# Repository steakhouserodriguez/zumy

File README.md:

# zumy
Zumy is a small robot running linux using Pololu's Zumo robot chassis.

For Instructions, see the [Wiki](https://github.com/andrewjchen/zumy/wiki)

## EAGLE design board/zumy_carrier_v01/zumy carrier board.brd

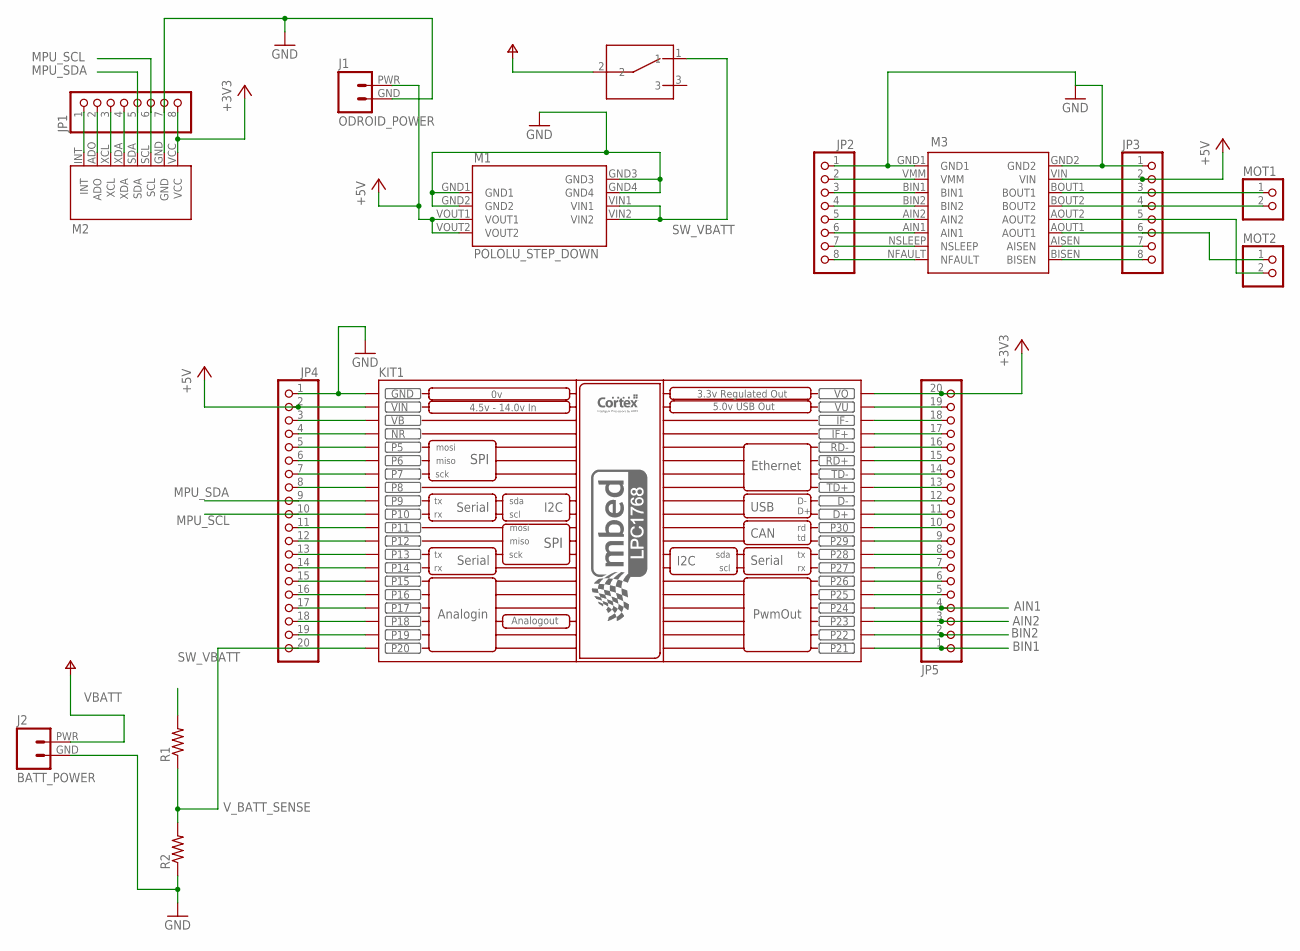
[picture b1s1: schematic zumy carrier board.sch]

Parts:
J1: ODROID_POWER; ODOIRD_PWR
J2: BATT_POWER
JP1, JP2, JP3: PINHD-1X8; 1X08
JP4, JP5: PINHD-1X20; 1X20
KIT1: MBED_NXP_LPC1768; MBED-KIT
M1: POLOLU_STEP_DOWN
M2: ITG/MPU_MODULE
M3: POLOLU_DRV8833_MODULE
MOT1, MOT2: PINHD-1X2; 1X02
R1, R2: R-US_0204/5; 0204/5
SW1: 500SSP1S1M6QEA; 500SSP1S1M6QEA_SWITCH

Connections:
+3V3: JP1.8, JP5.20, KIT1.VOUT (VO), M2.VCC
+5V: J1.PWR, JP3.2, JP4.2, KIT1.VIN, M1.VOUT1, M1.VOUT2, M3.VIN
AIN1: JP2.6, JP5.4, KIT1.P$24 (P24), M3.AIN1
AIN2: JP2.5, JP5.3, KIT1.P$23 (P23), M3.AIN2
BIN1: JP2.3, JP5.1, KIT1.P$21 (P21), M3.BIN1
BIN2: JP2.4, JP5.2, KIT1.P$22 (P22), M3.BIN2
GND: J1.GND, J2.GND, JP1.7, JP2.1, JP3.1, JP4.1, KIT1.GND, M1.GND1, M1.GND2, M1.GND3, M1.GND4, M2.GND, M3.GND1, M3.GND2, R2.1
MPU_SCL: JP1.6, JP4.10, KIT1.P$10 (P10), M2.SCL
MPU_SDA: JP1.5, JP4.9, KIT1.P$9 (P9), M2.SDA
unnamed: JP1.1, M2.INT
unnamed: JP1.2, M2.ADO
unnamed: JP1.3, M2.XCL
unnamed: JP1.4, M2.XDA
unnamed: JP4.15, KIT1.P$15 (P15)
unnamed: JP4.3, KIT1.VB
unnamed: JP4.4, KIT1.NR
unnamed: JP4.5, KIT1.P$5 (P5)
unnamed: JP4.6, KIT1.P$6 (P6)
unnamed: JP4.7, KIT1.P$7 (P7)
unnamed: JP4.8, KIT1.P$8 (P8)
unnamed: JP4.11, KIT1.P$11 (P11)
unnamed: JP4.12, KIT1.P$12 (P12)
unnamed: JP4.13, KIT1.P$13 (P13)
unnamed: JP4.14, KIT1.P$14 (P14)
unnamed: JP4.16, KIT1.P$16 (P16)
unnamed: JP4.17, KIT1.P$17 (P17)
unnamed: JP4.18, KIT1.P$18 (P18)
unnamed: JP4.19, KIT1.P$19 (P19)
unnamed: JP5.5, KIT1.P$25 (P25)
unnamed: JP5.6, KIT1.P$26 (P26)
unnamed: JP5.7, KIT1.P$27 (P27)
unnamed: JP5.8, KIT1.P$28 (P28)
unnamed: JP5.9, KIT1.P$29 (P29)
unnamed: JP5.10, KIT1.P$30 (P30)
unnamed: JP5.11, KIT1.D+
unnamed: JP5.12, KIT1.D-
unnamed: JP5.13, KIT1.TD+
unnamed: JP5.14, KIT1.TD-
unnamed: JP5.15, KIT1.RD+
unnamed: JP5.16, KIT1.RD-
unnamed: JP5.17, KIT1.IF+
unnamed: JP5.18, KIT1.IF-
unnamed: JP5.19, KIT1.VU
unnamed: JP2.2, M3.VMM
unnamed: JP2.7, M3.NSLEEP
unnamed: JP2.8, M3.NFAULT
unnamed: JP3.3, M3.BOUT1, MOT1.1
unnamed: JP3.4, M3.BOUT2, MOT1.2
unnamed: JP3.5, M3.AOUT2, MOT2.2
unnamed: JP3.6, M3.AOUT1, MOT2.1
unnamed: JP3.7, M3.AISEN
unnamed: JP3.8, M3.BISEN
SW_VBATT: M1.VIN1, M1.VIN2, R1.2, SW1.1
VBATT: J2.PWR, SW1.2
V_BATT_SENSE: JP4.20, KIT1.P$20 (P20), R1.1, R2.2

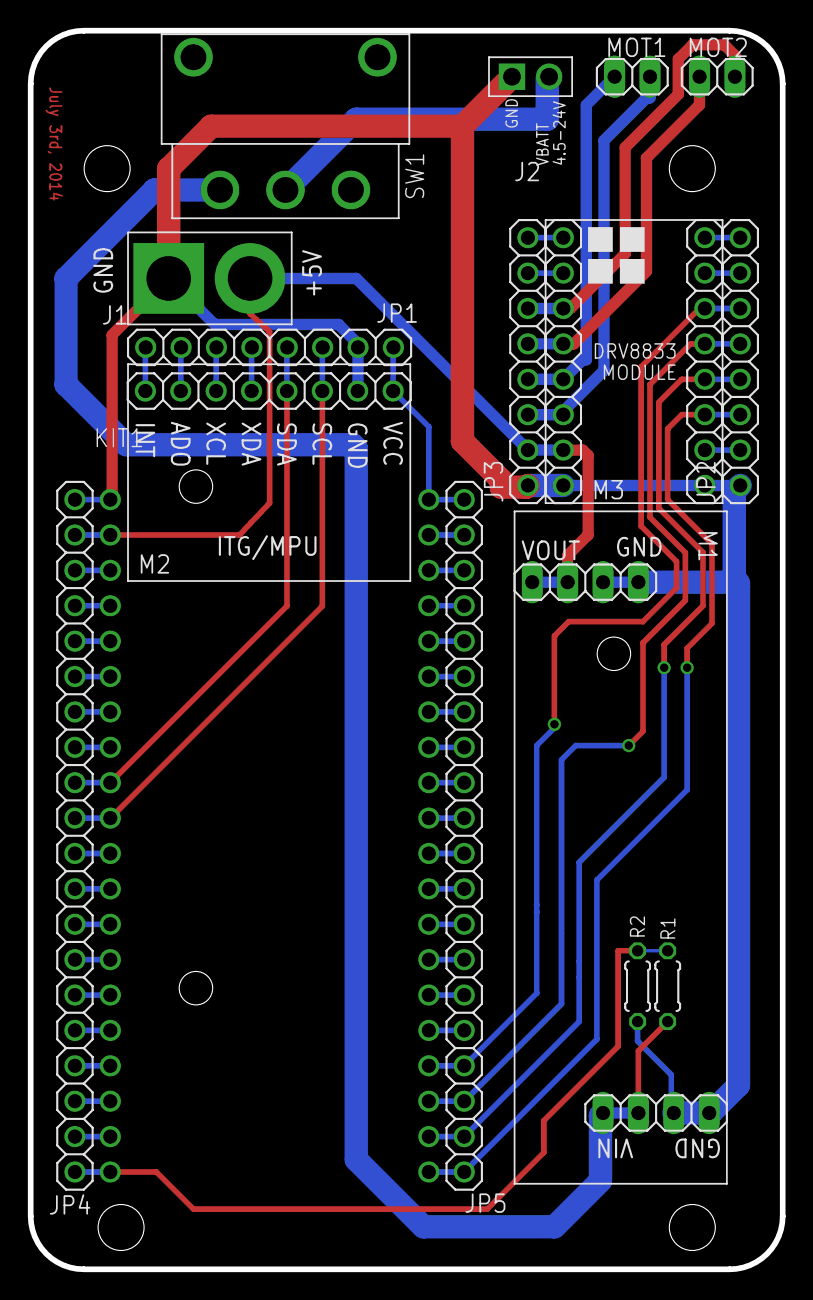
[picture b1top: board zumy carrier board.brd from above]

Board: 2 copper layers, 54.0 x 88.9 mm, 16 parts (0 on the bottom side), 55 nets.

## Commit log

2014-06-20 added gitignore
2014-06-20 linux state pub over lcm working on development machine
2014-06-20 linux state pub over lcm working on odroids with network restarting tools
2014-06-20 added simple joystick driver
2014-06-20 driving robots using mbed rpc and joystick commands
2014-06-20 added README
2014-06-20 Initial upload of carrier board schematic and layout, and parts library
2014-06-20 made joystick_mbed.py hardened for offline running
2014-06-20 added mbed setup notes
2014-06-23 initial ros package
2014-06-23 added zumy_cmd_joy to command robots from joystick
2014-06-23 added robot in vrep
2014-06-23 added sandcrawler_shell to zumocrawler model
2014-06-23 added lcm networking information to README.md
2014-07-03 Preliminary updates for rev c, unrouted.
2014-07-03 added rev c zumy carrier board
    expanded odroid power holes
    expanded battery power holes
    module layout change
    fixed switching cicuit to switch battery rather than ground
2014-10-29 added robust networking howto
2014-10-29 added docs for zumy_lcm_node.py
2014-10-29 added install instructions for screen and ssh
2014-10-29 removed lcm config
2014-10-29 various fixups for redoc tutorial
2014-10-30 fixed RobotCodeSetup.md from training session
2014-10-30 added fixes from training session
2014-11-02 added lcm recovery loops
2014-11-02 added throttle sweeps to test notebook
2014-11-08 running zumy_lcm_node.py as root
2014-11-08 renamed screen session to zumy_lcm_node in autostart
2014-11-08 removed prints from lcm_refresh
2014-11-08 added hostname setting
2014-11-08 added hostname setting to bringupFromImage
2014-11-08 moved docs to the wiki
2014-11-08 deprecated zc_id for system hostname
2014-11-08 updated notebook to reflect hostname ids

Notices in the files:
parts and their libraries:
biomimetic: UC Regents. All rights reserved.
